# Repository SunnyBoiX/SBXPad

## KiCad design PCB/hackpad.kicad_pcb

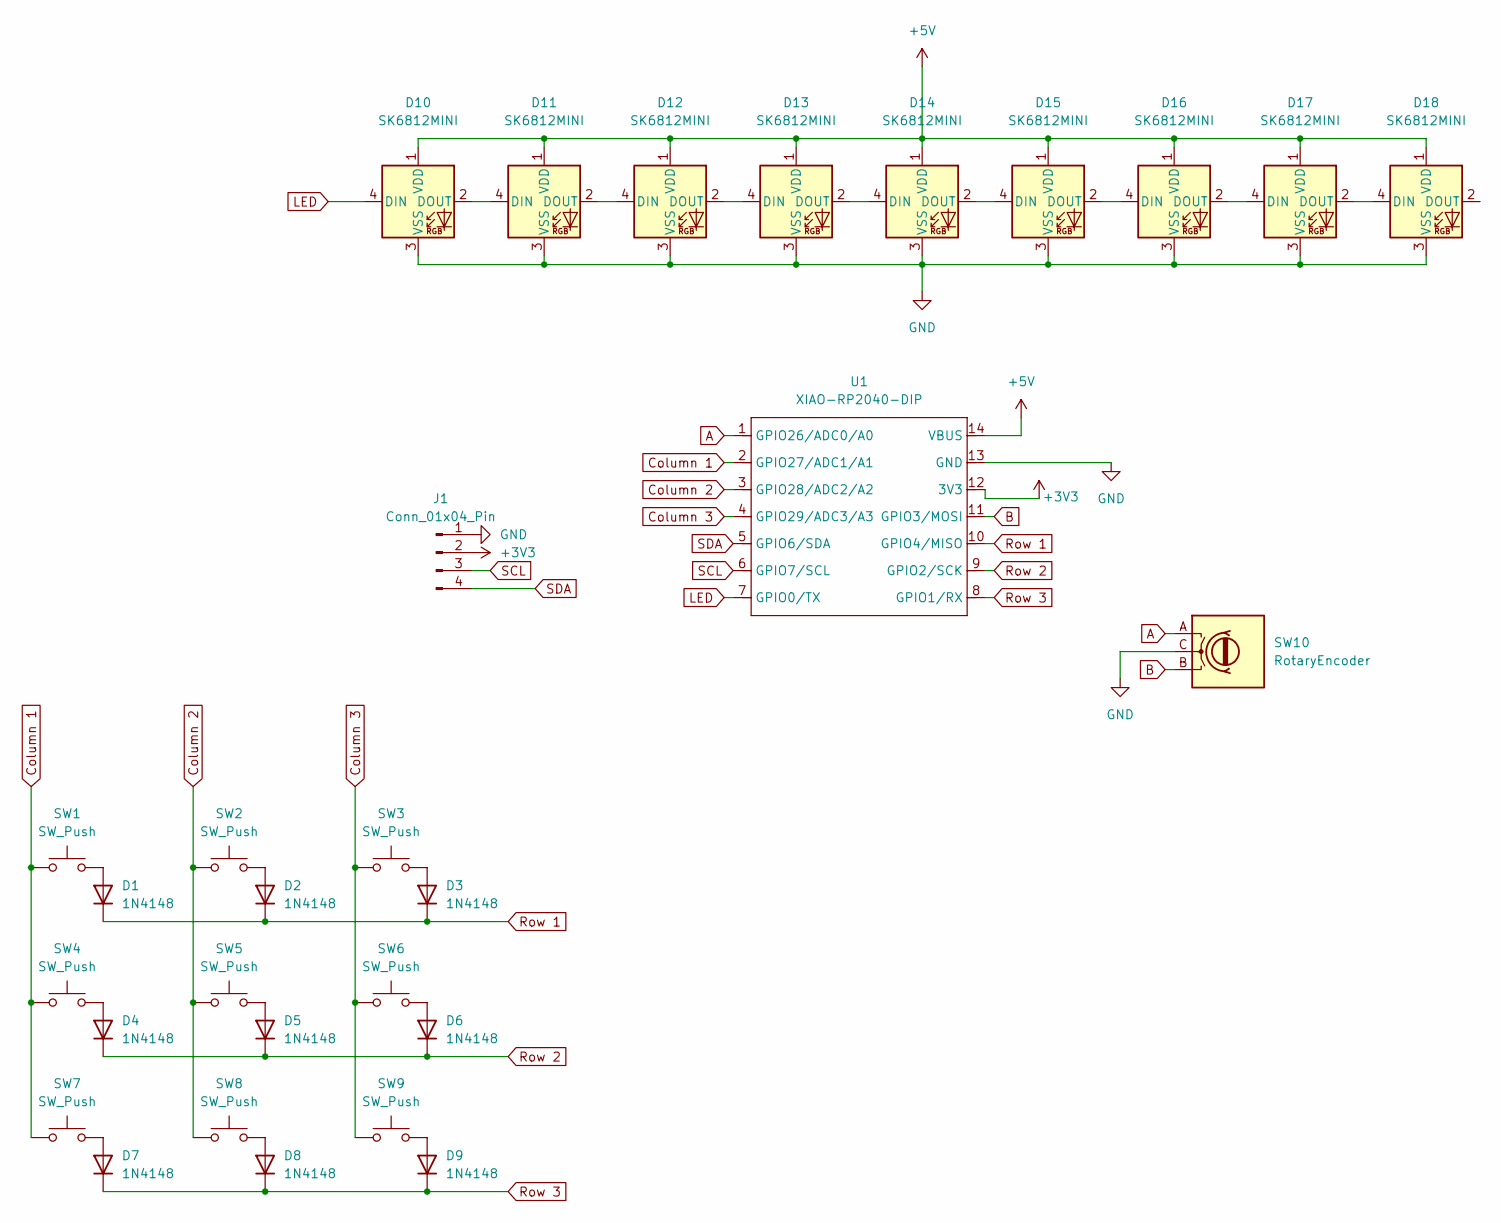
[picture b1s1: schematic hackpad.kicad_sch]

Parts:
D1, D2, D3, D4, D5, D6, D7, D8, D9: 1N4148; D_DO-35_SOD27_P7.62mm_Horizontal
D10, D11, D12, D13, D14, D15, D16, D17, D18: SK6812MINI; SK6812MINI-E_fixed
J1: Conn_01x04_Pin; SSD1306-0.91-OLED-4pin-128x32
SW1, SW2, SW3, SW4, SW5, SW6, SW7, SW8, SW9: SW_Push; SW_Cherry_MX_1.00u_PCB
SW10: RotaryEncoder; RotaryEncoder_Alps_EC11E-Switch_Vertical_H20mm
U1: XIAO-RP2040-DIP

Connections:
+3V3: J1.2, U1.12 (3V3)
+5V: D10.1 (VDD), D11.1 (VDD), D12.1 (VDD), D13.1 (VDD), D14.1 (VDD), D15.1 (VDD), D16.1 (VDD), D17.1 (VDD), D18.1 (VDD), U1.14 (VBUS)
A: SW10.A, U1.1 (GPIO26/ADC0/A0)
B: SW10.B, U1.11 (GPIO3/MOSI)
Column 1: SW1.2, SW4.2, SW7.2, U1.2 (GPIO27/ADC1/A1)
Column 2: SW2.2, SW5.2, SW8.2, U1.3 (GPIO28/ADC2/A2)
Column 3: SW3.2, SW6.2, SW9.2, U1.4 (GPIO29/ADC3/A3)
GND: D10.3 (VSS), D11.3 (VSS), D12.3 (VSS), D13.3 (VSS), D14.3 (VSS), D15.3 (VSS), D16.3 (VSS), D17.3 (VSS), D18.3 (VSS), J1.1, SW10.C, U1.13 (GND)
LED: D10.4 (DIN), U1.7 (GPIO0/TX)
unnamed: D1.2 (A), SW1.1
unnamed: D2.2 (A), SW2.1
unnamed: D3.2 (A), SW3.1
unnamed: D4.2 (A), SW4.1
unnamed: D5.2 (A), SW5.1
unnamed: D6.2 (A), SW6.1
unnamed: D7.2 (A), SW7.1
unnamed: D8.2 (A), SW8.1
unnamed: D9.2 (A), SW9.1
unnamed: D10.2 (DOUT), D11.4 (DIN)
unnamed: D11.2 (DOUT), D12.4 (DIN)
unnamed: D12.2 (DOUT), D13.4 (DIN)
unnamed: D13.2 (DOUT), D14.4 (DIN)
unnamed: D14.2 (DOUT), D15.4 (DIN)
unnamed: D15.2 (DOUT), D16.4 (DIN)
unnamed: D16.2 (DOUT), D17.4 (DIN)
unnamed: D17.2 (DOUT), D18.4 (DIN)
Row 1: D1.1 (K), D2.1 (K), D3.1 (K), U1.10 (GPIO4/MISO)
Row 2: D4.1 (K), D5.1 (K), D6.1 (K), U1.9 (GPIO2/SCK)
Row 3: D7.1 (K), D8.1 (K), D9.1 (K), U1.8 (GPIO1/RX)
SCL: J1.3, U1.6 (GPIO7/SCL)
SDA: J1.4, U1.5 (GPIO6/SDA)

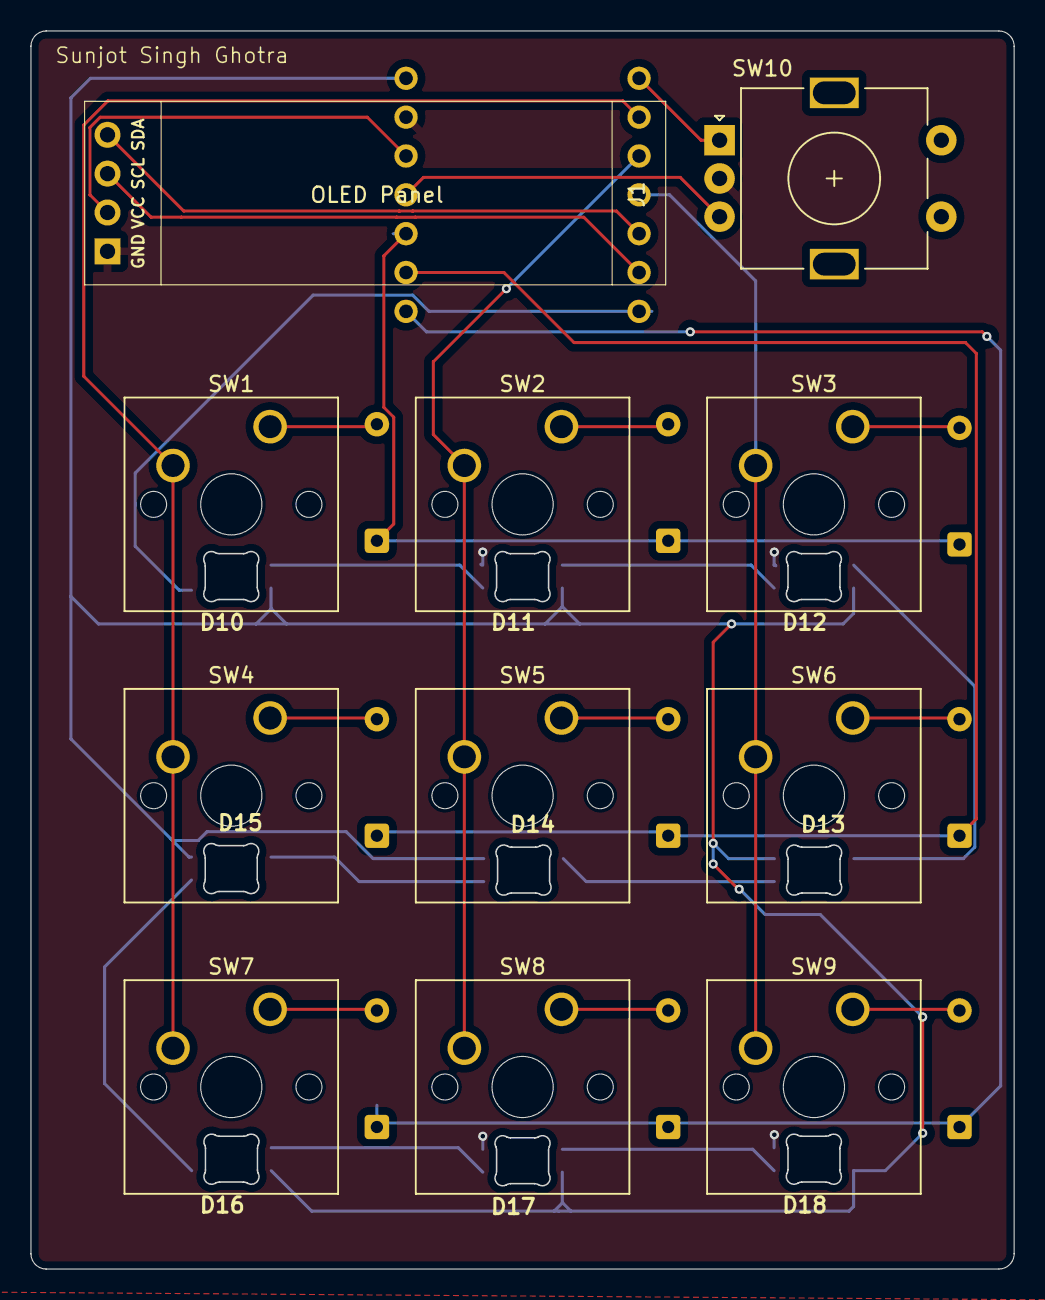
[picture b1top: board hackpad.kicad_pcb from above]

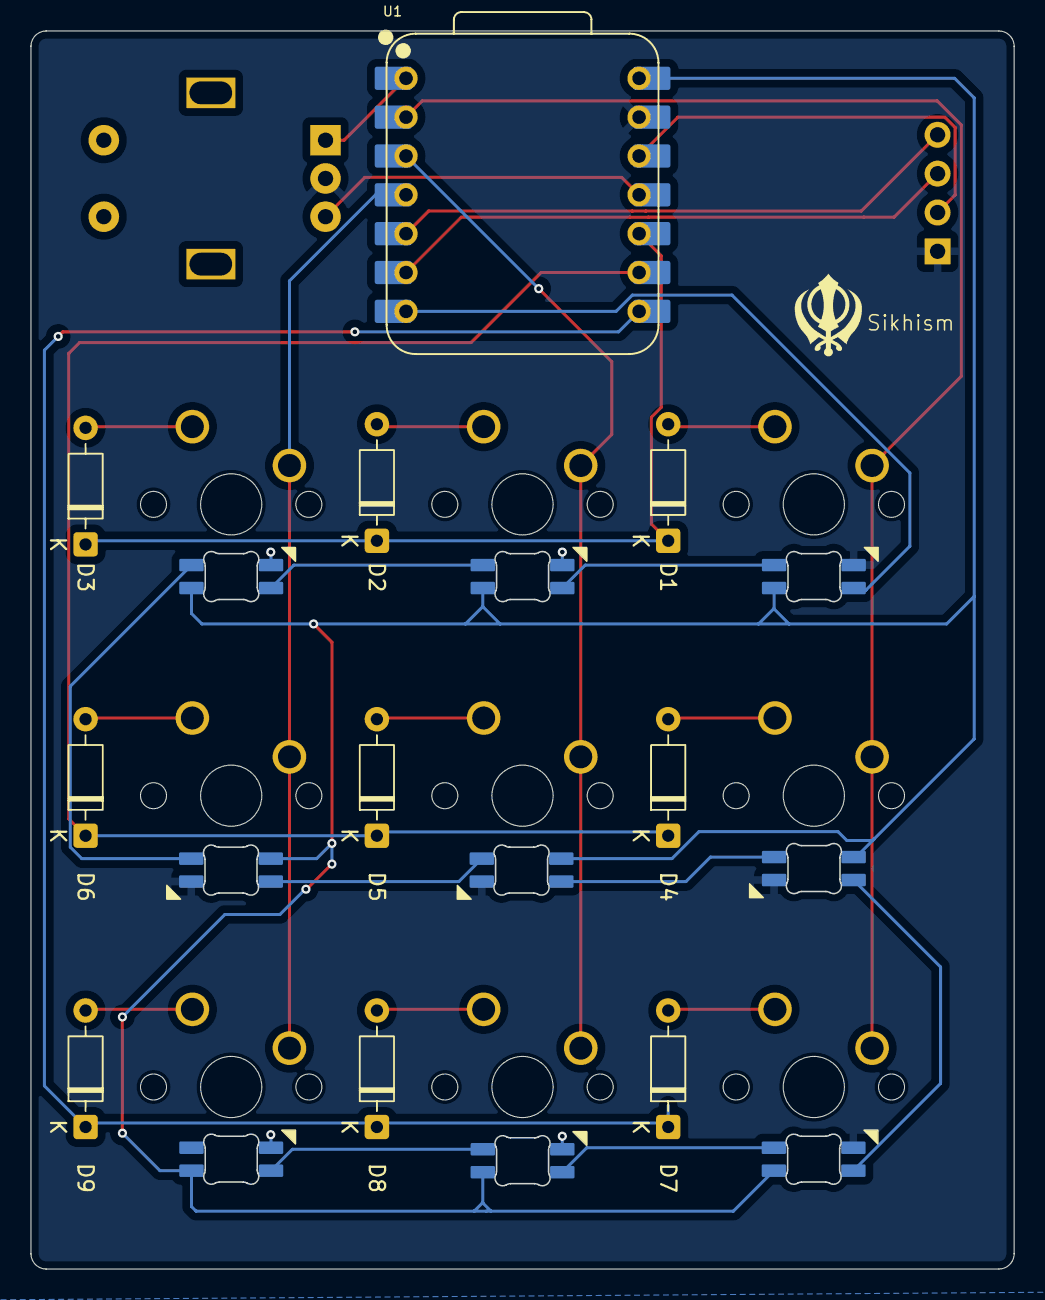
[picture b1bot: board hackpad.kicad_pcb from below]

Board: 2 copper layers, 64.2 x 80.9 mm, 30 parts (10 on the bottom side), 31 nets.

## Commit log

2026-04-01 Update project name in README
2026-04-01 Rename JOURNAL.md to test/JOURNAL.md
2026-04-01 Add initial PCB file description
2026-04-01 Initial SBXPad PCB Files
    - Uploaded core KiCad project, schematic, and board files.
    - Included library tables (fp/sym) to ensure footprints load correctly.
    - Added .prl workspace settings and the backups folder for routing history.
2026-04-01 Create hackpad-backups
2026-04-01 Add test.txt with initial content
2026-04-01 Add PCB design backups
    Uploaded the backups folder for routing history.
